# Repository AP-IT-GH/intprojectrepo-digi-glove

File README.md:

# DigiGlove
With this project we try to make a digital glove which can be used to perform macro's.

## General Information
### Privacy Policy
If you want to learn more about our privacy policy, open the following file:
- 'PRIVACYPOLICY_DigiGlove.docx'

### Manual of the Application (GUI)
If you want to learn more about how to use the application or GUI (=Graphic User Interface), open the following file:
- 'ManualDigiGloveApplication.docx'

### Manual of the Glove
- information follows

## The Project
### Connections
#### Connection between the glove and the computer
The connection between the glove and the computer ensures a channel through which data is continuously send.
This is a Bluetooth module. The Bluetooth-transmitter (the glove) sends captured data continuously to the Bluetooth-receiver (a COM-port on the PC).

#### Connection between the GUI and the running script
The connection between the GUI is used to transfer settings/ a configuration to the script.
This connection gets made by using a network socket. The user has to establish a connection between the two parties in the GUI. One of the parties is the Application, the other party is the running script. A string of data with the specifications gets send to the running program.

### Handeling the data
The task of handeling the data is to provide a continuous flow of data, so the variables are up-to-date.
When the data is received on the PC, it gets structured in variables. The continuous updates override the values of the variables each time there is an update. This process gets done by a thread called updateThread in the project.

These values get passed on to the validation variables. This is also a continuous process which is done by another thread called updateFingers in the project. It ensures that the validation variables are always up to date with the latest values received from the glove.

### Validating the data
The task of the validation is to define whether a macro has to be executed or not.
The validation gets done by another thread. This thread is called validationFingers. It’s a continuous loop that checks if the values of certain variables are higher than certain border point. For example you are validating a finger. Once the value of the finger reaches the border point, the finger is seen as bended.
If the validation is true, a corresponding macro gets called and is executed.

### Configuration of the GUI
The task of the GUI is to configure the glove's settings:
- In the GUI you can create as many macro's as you want by using a "+" sign as seperator or without create automatic typed messages
- You can choose which macro you want to assign to each finger
- Your able to overlay as many macros as you want on each finger.

When you have made a configuration and press the save button, the configuration gets passed on to the program via a network socket (as beeing explained in the connections part).

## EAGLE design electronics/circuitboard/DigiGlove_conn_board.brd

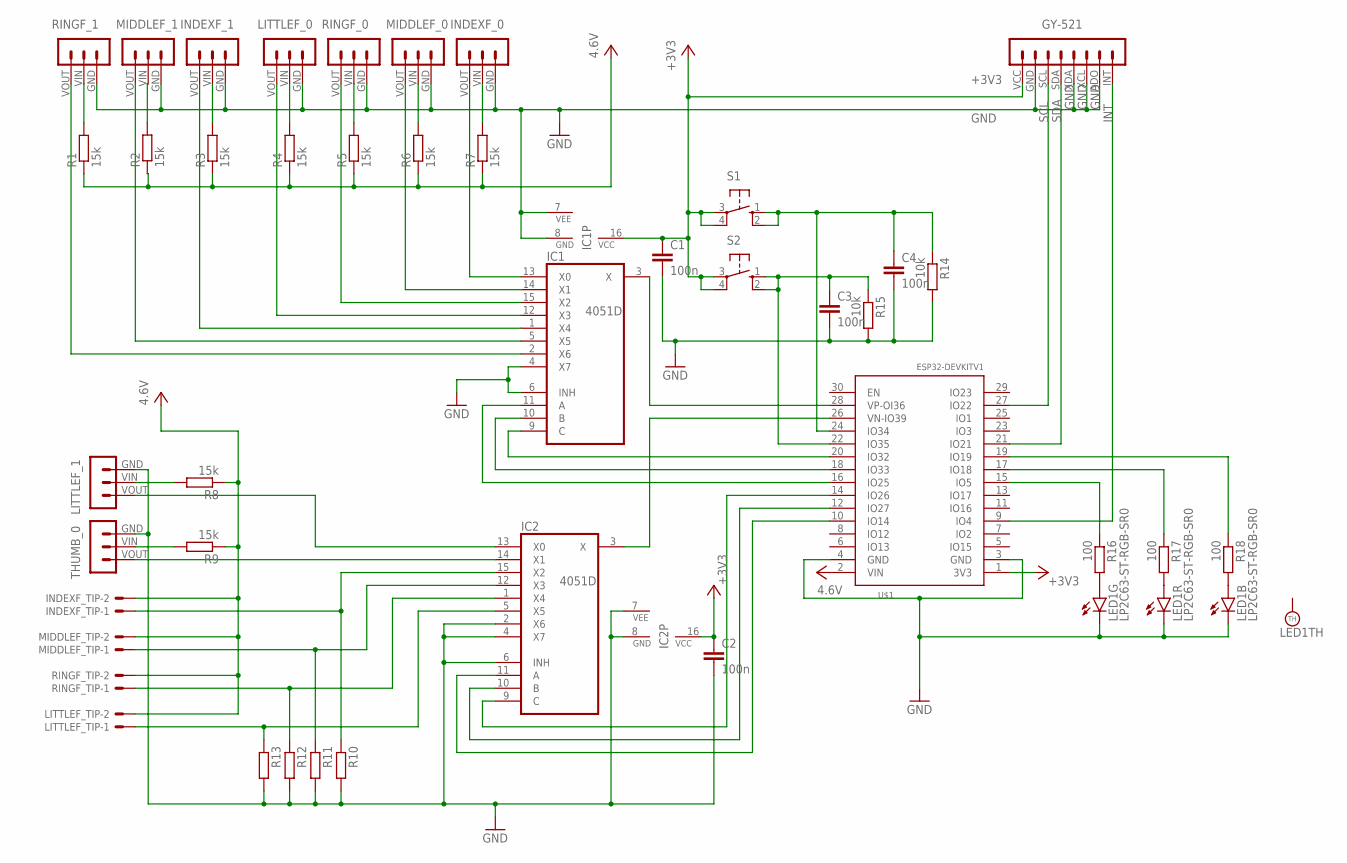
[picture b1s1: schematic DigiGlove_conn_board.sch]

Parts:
C1, C2, C3, C4: 100n; C1608
GY-521: MA08-1MA08-1_254; PAD8_254
IC1, IC2: 4051D; SO16
INDEXF_0, INDEXF_1: MA03-1MA03-1-254; PAD3_254
INDEXF_TIP: 22-23-20212PIN_254; PAD2_254
LED1: LP2C63-ST-RGB-SR0
LITTLEF_0, LITTLEF_1: MA03-1MA03-1-254; PAD3_254
LITTLEF_TIP: 22-23-20212PIN_254; PAD2_254
MIDDLEF_0, MIDDLEF_1: MA03-1MA03-1-254; PAD3_254
MIDDLEF_TIP: 22-23-20212PIN_254; PAD2_254
R1, R2, R3, R4, R5, R6, R7, R8, R9: 15k; R2012
R10, R11, R12, R13: R-EU_R2012; R2012
R14, R15: 10k; R2012
R16, R17, R18: 100; R0603
RINGF_0, RINGF_1: MA03-1MA03-1-254; PAD3_254
RINGF_TIP: 22-23-20212PIN_254; PAD2_254
S1, S2: 10-XX; B3F-10XX
THUMB_0: MA03-1MA03-1-254; PAD3_254
U$1: ESP32DEVKITV1HEADER; MA17-2

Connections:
+3V3: C1.1, C2.1, GY-521.VCC, IC1.16 (VCC), IC2.16 (VCC), S1.3, S1.4 (P1), S2.3, S2.4 (P1), U$1.1 (3V3)
GND: C1.2, C2.2, C3.2, C4.2, GY-521.ADO, GY-521.GND, GY-521.XCL, GY-521.XDA, IC1.4 (X7), IC1.6 (INH), IC1.7 (VEE), IC1.8 (GND), IC2.2 (X6), IC2.4 (X7), IC2.6 (INH), IC2.7 (VEE), IC2.8 (GND), INDEXF_0.GND, INDEXF_1.GND, LED1.4 (C), LED1.5 (C), LED1.6 (C), LITTLEF_0.GND, LITTLEF_1.GND, MIDDLEF_0.GND, MIDDLEF_1.GND, R10.2, R11.2, R12.2, R13.2, R14.2, R15.2, RINGF_0.GND, RINGF_1.GND, THUMB_0.GND, U$1.3 (GND), U$1.4 (GND)
INT: GY-521.INT, U$1.9 (IO4)
unnamed: IC1.13 (X0), INDEXF_0.VOUT
unnamed: IC1.14 (X1), MIDDLEF_0.VOUT
unnamed: IC1.15 (X2), RINGF_0.VOUT
unnamed: IC1.12 (X3), LITTLEF_0.VOUT
unnamed: IC1.1 (X4), INDEXF_1.VOUT
unnamed: IC1.5 (X5), MIDDLEF_1.VOUT
unnamed: IC1.2 (X6), RINGF_1.VOUT
unnamed: IC2.5 (X5), LITTLEF_TIP.P$1, R13.1
unnamed: IC2.1 (X4), R12.1, RINGF_TIP.P$1
unnamed: IC2.12 (X3), MIDDLEF_TIP.P$1, R11.1
unnamed: IC2.15 (X2), INDEXF_TIP.P$1, R10.1
unnamed: R1.2, RINGF_1.VIN
unnamed: MIDDLEF_1.VIN, R2.2
unnamed: INDEXF_1.VIN, R3.2
unnamed: LITTLEF_0.VIN, R4.2
unnamed: R5.2, RINGF_0.VIN
unnamed: MIDDLEF_0.VIN, R6.2
unnamed: INDEXF_0.VIN, R7.2
unnamed: IC2.14 (X1), THUMB_0.VOUT
unnamed: IC2.13 (X0), LITTLEF_1.VOUT
unnamed: R9.2, THUMB_0.VIN
unnamed: LITTLEF_1.VIN, R8.2
unnamed: IC1.3 (X), U$1.28 (VP-OI36)
unnamed: IC2.3 (X), U$1.26 (VN-IO39)
unnamed: IC1.9 (C), U$1.20 (IO32)
unnamed: IC1.10 (B), U$1.18 (IO33)
unnamed: IC1.11 (A), U$1.16 (IO25)
unnamed: C4.1, R14.1, S1.1 (S), S1.2 (S1), U$1.24 (IO34)
unnamed: IC2.9 (C), U$1.14 (IO26)
unnamed: IC2.10 (B), U$1.12 (IO27)
unnamed: IC2.11 (A), U$1.10 (IO14)
unnamed: C3.1, R15.1, S2.1 (S), S2.2 (S1), U$1.22 (IO35)
unnamed: R16.1, U$1.15 (IO5)
unnamed: R17.1, U$1.17 (IO18)
unnamed: R18.1, U$1.19 (IO19)
unnamed: LED1.1 (A), R16.2
unnamed: LED1.2 (A), R17.2
unnamed: LED1.3 (A), R18.2
SCL: GY-521.SCL, U$1.27 (IO22)
SDA: GY-521.SDA, U$1.21 (IO21)
VCC: INDEXF_TIP.P$2, LITTLEF_TIP.P$2, MIDDLEF_TIP.P$2, R1.1, R2.1, R3.1, R4.1, R5.1, R6.1, R7.1, R8.1, R9.1, RINGF_TIP.P$2, U$1.2 (VIN)

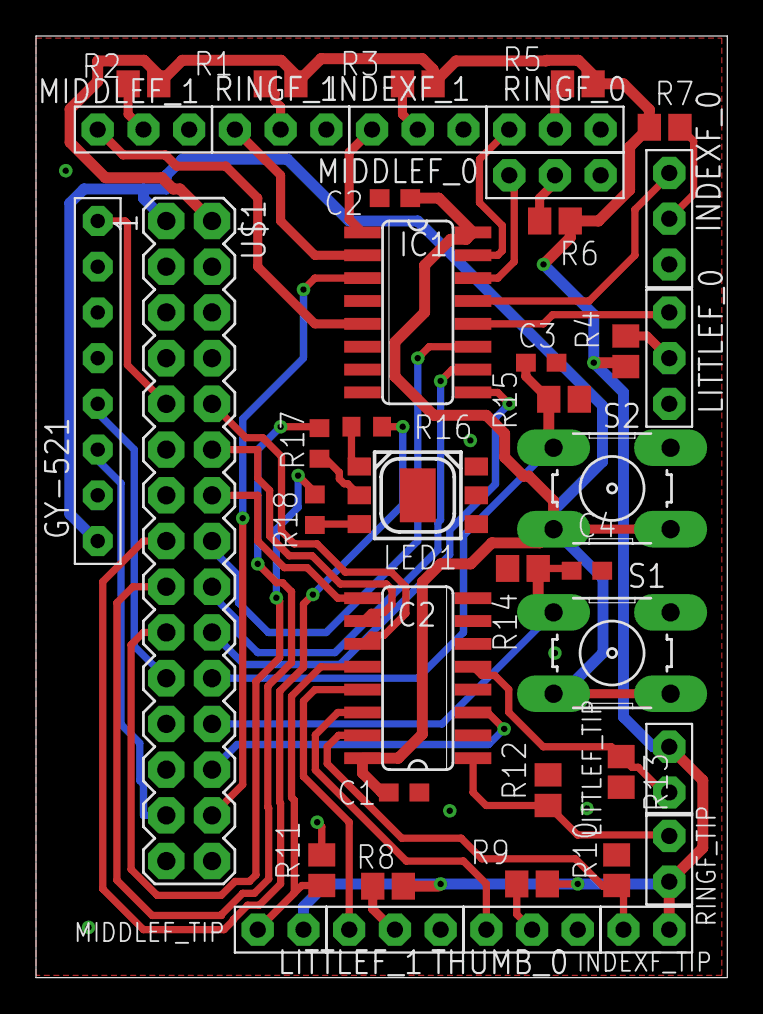
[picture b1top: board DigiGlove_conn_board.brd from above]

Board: 2 copper layers, 38.4 x 52.3 mm, 42 parts (0 on the bottom side), 44 nets.

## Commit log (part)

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2020-02-04 Project Idea Doc
2020-02-04 Update and commiting of the right doc file
2020-02-04 Update to project idea
2020-02-05 a few edits
    bluetooth in c# should be able to scan on any computer that has bluetooth with Microsoft's drivers
2020-02-21 bluetooth save
    simple save of progress
2020-02-28 expanded on bluetooth
    added a few methods and an example data dictionairy
2020-03-01 restructured folders
2020-03-01 added esp-idf as submodule
2020-03-01 initialized glove-mcu folder
2020-03-01 updated gitignore
2020-03-03 Creation of Winform Application with basic features
    A winform application that contains navigational menu,
2020-03-03 Macro bestand toegevoegd
2020-03-09 Removed submodule esp32/esp-idf
2020-03-09 fixing error
2020-03-09 Data Processing
2020-03-09 Data Processing 2
2020-03-09 Made connection between finger and macro
2020-03-09 BugFix Data Processing
2020-03-10 Other Fingers
2020-03-10 Updating .gitignore to match masters
    This should hopefully solve this esp32 mess on my side
2020-03-10 bug fixed
2020-03-10 Removed .vs folder from repository
2020-03-10 bluetooth works
    bluetooth works
2020-03-10 forgot to save
    yes i am a human i make mistakes
2020-03-10 Revert "Fix"
    This reverts commit ff709d54c1ad9b9dd384a0ab67571451f9fa81e8.
2020-03-10 Revert "Revert "Fix""
    This reverts commit a025d9b2b432b7c46c3d46d87ab915bc21c8bcc2.
2020-03-10 Revert "bluetooth works"
    This reverts commit e378234a3672f72b054edf9deb376d889557675b.
2020-03-10 Deleting all of python101 to be commited again without unnecessary files
2020-03-11 Modified libraries to support DMP version 6.12
2020-03-12 Partially ported arduino example for DMP 6.12, ypr now works
2020-03-18 Basefile for communication between ESP32 and laptop
2020-03-18 Corrected COM ports
2020-03-20 initializing esp branch
2020-03-21 Beginning of socket code
2020-03-22 Removing configuration files
2020-03-23 Auto stash before merge of "master" and "origin/master"
2020-03-23 Got rid off errors
2020-03-23 Updated Configuration with connect and send button
    The buttons are poorly aligned With the form but allow for manual connecting of the socket client and sending data over the connection
2020-03-23 Adapt .ignore
2020-03-23 Got all up and running
    The Bluetooth data transferred from the ESP is now stored in the dictionary when you run the update method the code isn't hard yet it is hardcoded as that is the simpelest method. this code can be mo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
2020-03-23 Now able to call the function from GUI
2020-03-25 Changed Gitignore, to include software/ again.
2020-03-25 Removed unused submodule
2020-03-25 initializing esp32 folder. Added required libraries
2020-03-25 Fixed packet being wrong
2020-03-25 Modified sdkconfig for PlatformIO with classic BT
2020-03-25 Added bluetooth SPP code
2020-03-25 Deleted IMU stuff from BT branch
2020-03-25 Modified packet structure and only index finger does a quick bend now
2020-03-25 Moved dummy data program to BT_dummy
2020-03-26 Added Macro to pause glove
    changed working folders, everyone has to work in marco.py in the python101 map. Added a Macro to pause the glove's functionalities.
2020-03-27 Added bt_spp files with bt_init and bt_create_packet functions
2020-03-27 Changed to fixed PIN
2020-03-27 Made macros usable
2020-03-28 Added Bluetooth Update
    Added import of Quinten. To make the program work more efficient I'll make a thread so the update process can run concurrently with the rest of the program.
2020-03-28 Temporary Function
2020-03-29 Added Macro to Application
    Added the macro "PauseGlove" to list of macro's in the application
2020-03-30 Added threading
    The project is able to be run some functions concurrently
2020-03-30 Final Push
    Final push so Quinten can test it all.
2020-03-30 Transferred main thread
    The main thread is now in Macros.py and can run the code in python101.py
2020-03-31 Made the script work without hardware and removed the lock in the thread
2020-03-31 All issues resolved
    fixed threads locking, main thread now starts in python101.py and is transferred to the Macro's file in the first few lines.
    data now comes through as all 0 without a device instead of crashing the script.
    sockets have been moved to the bottom of the file to make sure the background threads are started properly
    any issues be sure to ask me.
2020-03-31 Prepping for the latest test data
2020-03-31 Frequency tuning for update method
2020-03-31 Bug fixed, crash upon receiving socket message.
2020-04-03 Added PCB files
2020-04-04 --GENERAL-- Deleted unused files Moved packet declaration to its own .h file Added pins.h Added dummydata generation functionality --SENSORS.C-- Fixed logic errors Removed magic numbers Added functio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
2020-04-06 Increased app partition size to 3.8M
2020-04-06 The user gets more feedback
    Once a user has made connection with the glove to transfer the configuration settings, the connect button gets disabled.
2020-04-09 Modified to reflect changes in the packet structure and renamed confusing define
2020-04-10 Added debug printing functionality
2020-04-10 Moved bluetooth_spp_property structure from .h to .c to fix multiple definitions error. Removed unused variable
2020-04-10 Enabled colorized console output
2020-04-10 Added basic IMU functionality
2020-04-10 added IMU checks for troubleshooting
2020-04-10 corrected pin configuration and updated errorcheck
2020-04-10 Added RGB led control functions
2020-04-10 Updated for new packet
    Updated the Python101 file to support the new packet order and size.
2020-04-10 Solved a bug
    Corrected a variable name
2020-04-10 Adapted to new package
2020-04-10 Corrected communication to small endian.
    All communication is now up to date and hopefully free of bugs.
2020-04-10 Fixed packet size and offsets
2020-04-17 bugfixing
2020-04-18 Recreated the python-dev branch and project .
    as i accidentally removed the python project file from the program, i recreated it now. with the code as up to date as possible
2020-04-18 Added the PrivacyPolicy
    This file contains the Privacy Policy of DigiGlove.
2020-04-18 Update README
    Made a clearer overview of the project's tasks (for the Belgian students).
2020-04-18 Small changes (2)
2020-04-19 Changers Thread
2020-04-19 Corrected RGB LED pins
2020-04-19 IMU bugfixing, should now be 100Hz
2020-04-19 Changes to the READ.ME (3)
2020-04-19 Changes READ.ME
2020-04-19 Changes PauseGlove
2020-04-19 first Macro's operational
    The first Macro's are now executed straight from the dummy data. ready for the actual hardware to arrive.
2020-04-19 Dynamic Macro creation Front End 1
    Started with the cleanup of visual errors and I polished the look a bit .
    I added a button to create an empty macro template and added a save functionality so that created macro's remain over shut down and startup.
2020-04-19 Deleted irrelevant old code.
    Deleted old code files for less confusion.
2020-04-19 scipt
2020-04-19 Fixed some lines, corrected pins
2020-04-20 imports en includes
2020-04-20 Dynamic Macro Creation Front End 2
    Finished visual layout, just waiting for transition on the python End. The socket communication has been unchanged
2020-04-21 Script verplaatst en some math
2020-04-21 debugging Mousemove
    find out the issues with mousemove and correct them.
2020-04-22 cleaning and tidying, removing unnecessary variables and prints
2020-04-22 slight edit to split long lines to improve readability
2020-04-22 added led init, button task and required headers
2020-04-23 First version Usage Glove
2020-04-24 smal bugfix
2020-04-24 brol cleanup
2020-04-25 Cleanup comment code
2020-04-25 not work ignore
2020-04-25 pls work
2020-04-25 Live_debug
    editing Macro's for live debug
2020-04-25 made the variables update throughout the code
2020-04-25 Merge
2020-04-25 finger_debug
2020-04-25 Changed Static Macro to Dynamic Macro
    -Redisigned code to work with any macro
    -Updated UI ellements to work better with new implementation
2020-04-25 Added information to info page + extra feature
    -Notification boxes when disconnected from python code
    -Notification boxes when deleting a macro
2020-04-26 added input for com port number
    you are now supposed to enter a number before the script continues
2020-04-26 charlie's greatest hits
2020-04-26 Update to the finishing layout of the GUI. TODO: home page
2020-04-26 kleine aanpassing
2020-04-27 Added Setup Files to distibute Program
2020-04-27 Deleted Tkinter from py files
2020-04-27 Updated python files
2020-04-27 Change back to debug style of working
2020-04-27 Edited port definition and tweaked mouse logic
2020-04-27 Made it possible to update running configuration of macros
2020-04-27 Solved a bug where no mouseclick was possible
2020-04-27 debugging
2020-04-28 latest changes
2020-04-28 Updated for Jaakko
2020-04-29 Only the byebye video
    Only the byebye video is small enough to be pushed in the repo :)
2021-03-19 Bump pillow from 7.1.2 to 8.1.1 in /software/Digi-Glove-Application
    Bumps [pillow](https://github.com/python-pillow/Pillow) from 7.1.2 to 8.1.1.
    - [Release notes](https://github.com/python-pillow/Pillow/releases)
    - [Changelog](https://github.com/python-pillow/Pillow/blob/master/CHANGES.rst)
    - [Commits](https://github.com/python-pillow/Pillow/compare/7.1.2...8.1.1)
2021-06-08 Bump pillow from 7.1.2 to 8.2.0 in /software/Digi-Glove-Application
    Bumps [pillow](https://github.com/python-pillow/Pillow) from 7.1.2 to 8.2.0.
    - [Release notes](https://github.com/python-pillow/Pillow/releases)
    - [Changelog](https://github.com/python-pillow/Pillow/blob/master/CHANGES.rst)
    - [Commits](https://github.com/python-pillow/Pillow/compare/7.1.2...8.2.0)
    ---
    updated-dependencies:
2021-08-09 Bump pywin32 from 227 to 301 in /software/Digi-Glove-Application
    Bumps [pywin32](https://github.com/mhammond/pywin32) from 227 to 301.
    - [Release notes](https://github.com/mhammond/pywin32/releases)
    - [Changelog](https://github.com/mhammond/pywin32/blob/master/CHANGES.txt)
    - [Commits](https://github.com/mhammond/pywin32/commits)
    ---
    updated-dependencies:
2022-01-13 Bump pillow from 7.1.2 to 9.0.0 in /software/Digi-Glove-Application
    Bumps [pillow](https://github.com/python-pillow/Pillow) from 7.1.2 to 9.0.0.
    - [Release notes](https://github.com/python-pillow/Pillow/releases)
    - [Changelog](https://github.com/python-pillow/Pillow/blob/main/CHANGES.rst)
    - [Commits](https://github.com/python-pillow/Pillow/compare/7.1.2...9.0.0)
    ---
    updated-dependencies:
2022-03-12 Bump pillow from 7.1.2 to 9.0.1 in /software/Digi-Glove-Application
    Bumps [pillow](https://github.com/python-pillow/Pillow) from 7.1.2 to 9.0.1.
    - [Release notes](https://github.com/python-pillow/Pillow/releases)
    - [Changelog](https://github.com/python-pillow/Pillow/blob/main/CHANGES.rst)
    - [Commits](https://github.com/python-pillow/Pillow/compare/7.1.2...9.0.1)
    ---
    updated-dependencies:
2022-06-22 Bump Newtonsoft.Json in /software/Digi-Glove-Application
    Bumps [Newtonsoft.Json](https://github.com/JamesNK/Newtonsoft.Json) from 12.0.3 to 13.0.1.
    - [Release notes](https://github.com/JamesNK/Newtonsoft.Json/releases)
    - [Commits](https://github.com/JamesNK/Newtonsoft.Json/compare/12.0.3...13.0.1)
    ---
    updated-dependencies:
    - dependency-name: Newtonsoft.Json
